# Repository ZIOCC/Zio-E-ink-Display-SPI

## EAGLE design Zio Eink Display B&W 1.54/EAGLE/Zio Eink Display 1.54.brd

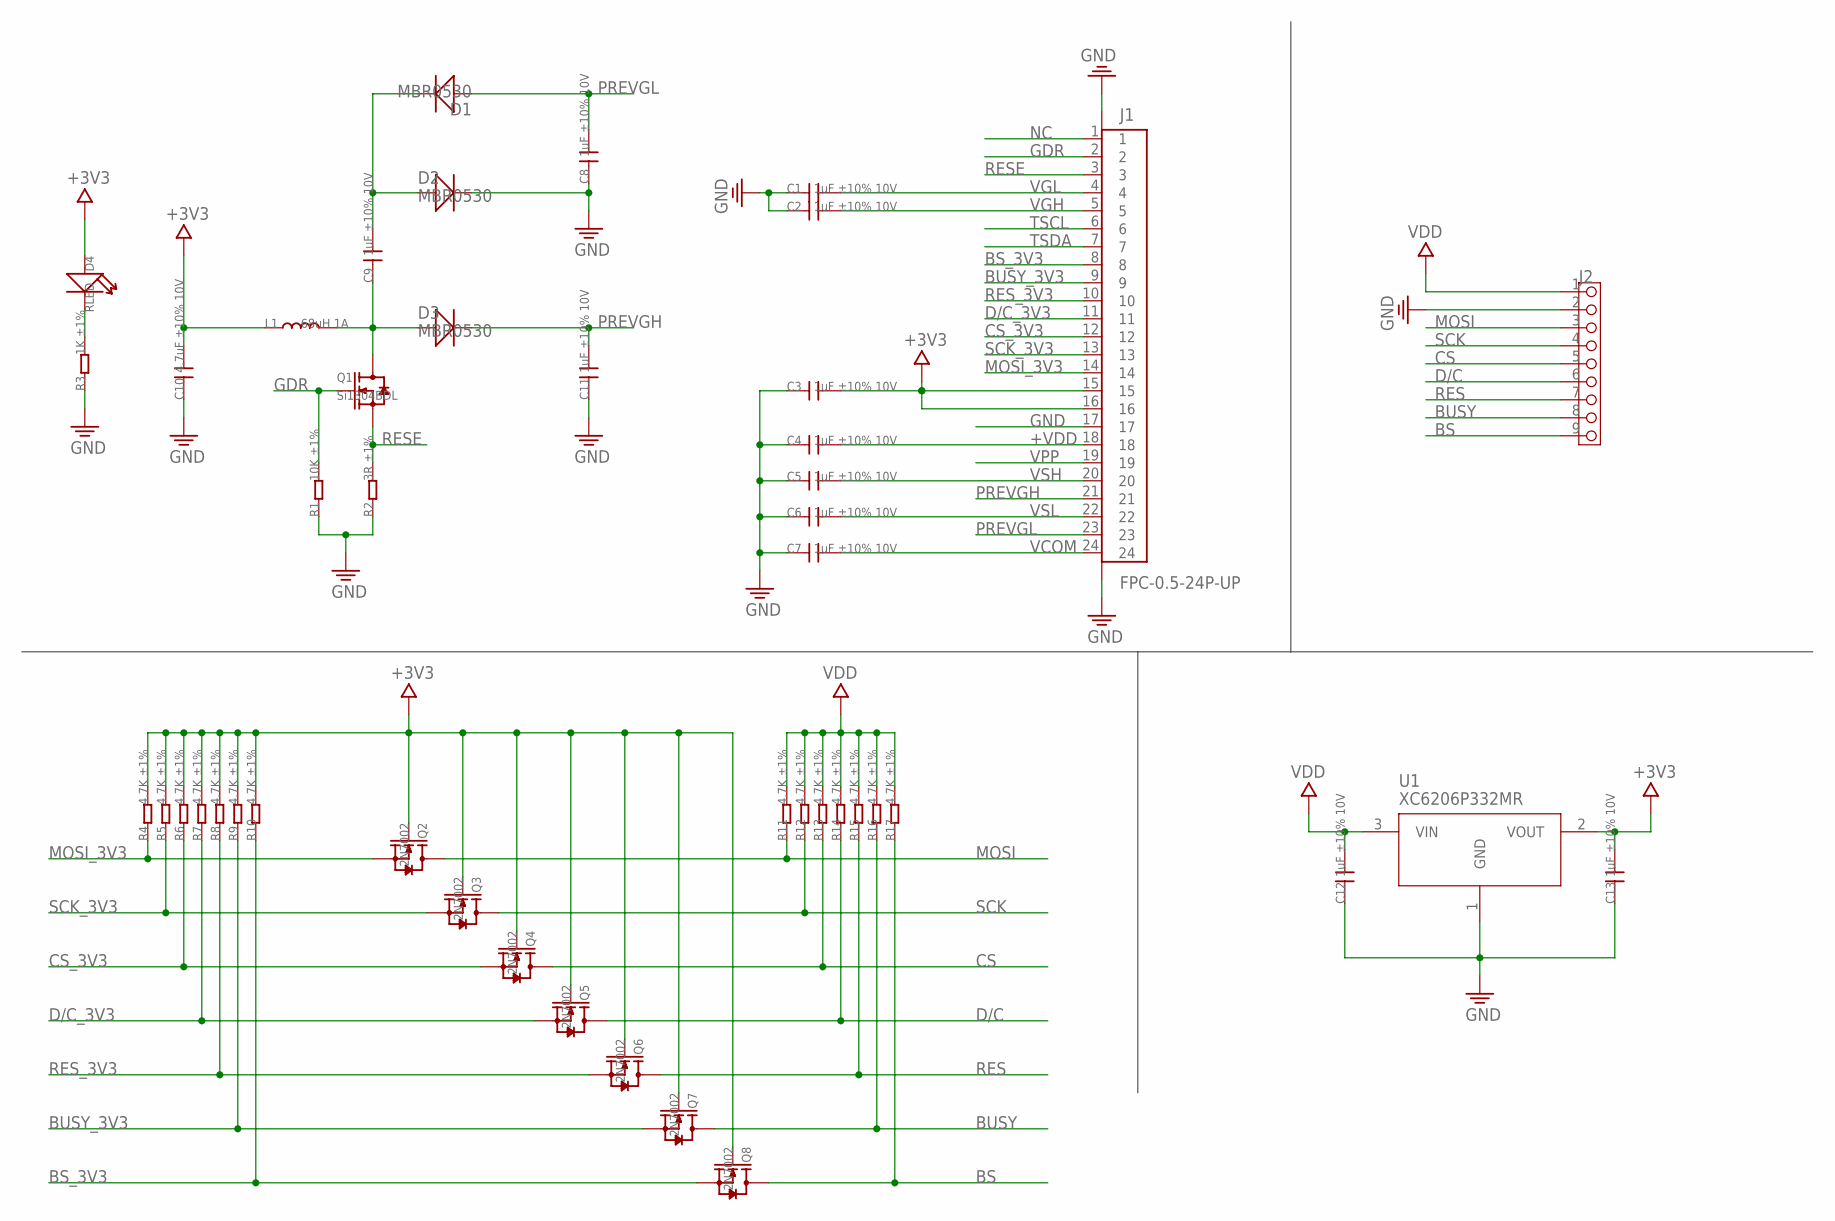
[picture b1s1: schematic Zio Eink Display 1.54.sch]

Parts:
C1, C2, C3, C4, C5, C6, C7, C8, C9, C11, C12, C13: 1uF ±10% 10V; 0603
C10: 4.7uF ±10% 10V; 0603
D1, D2, D3: MBR0530; SOD123
D4: RLED; LED-0603
J1: FPC-0.5-24P-UP; FPC-0.5-24P_UP
J2: HEADER-9P2.54; 9P-2.54-SMD
L1: 68uH 1A; L3012
Q1: Si1304BDL; SOT-323
Q2, Q3, Q4, Q5, Q6, Q7, Q8: 2N7002; SOT23
R1: 10K ±1%; 0603
R2: 3R ±1%; 0603
R3: 1K ±1%; 0402
R4, R5, R6, R7, R8, R9, R10, R11, R12, R13, R14, R15, R16, R17: 4.7K ±1%; 0402
U1: XC6206P332MR; SOT23

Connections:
+3V3: C3.2, C10.2, C13.2, D4.+, J1.15, J1.16, L1.P$1 (1), Q2.1 (G), Q3.1 (G), Q4.1 (G), Q5.1 (G), Q6.1 (G), Q7.1 (G), Q8.1 (G), R4.2, R5.2, R6.2, R7.2, R8.2, R9.2, R10.2, U1.2 (VOUT)
+VDD: C4.2, J1.18
BS: J2.9, Q8.3 (D), R17.1
BS_3V3: J1.8, Q8.2 (S), R10.1
BUSY: J2.8, Q7.3 (D), R16.1
BUSY_3V3: J1.9, Q7.2 (S), R9.1
CS: J2.5, Q4.3 (D), R13.1
CS_3V3: J1.12, Q4.2 (S), R6.1
D/C: J2.6, Q5.3 (D), R14.1
D/C_3V3: J1.11, Q5.2 (S), R7.1
GDR: J1.2, Q1.1 (G), R1.2
GND: C1.1, C2.1, C3.1, C4.1, C5.1, C6.1, C7.1, C8.1, C10.1, C11.1, C12.1, C13.1, D2.-, J1.17, J1.25 (G1), J1.26 (G2), J2.2, R1.1, R2.1, R3.1, U1.1 (GND)
MOSI: J2.3, Q2.3 (D), R11.1
MOSI_3V3: J1.14, Q2.2 (S), R4.1
unnamed: C9.2, D1.-, D2.+
unnamed: C9.1, D3.+, L1.P$2 (2), Q1.3 (D)
unnamed: D4.-, R3.2
NC: J1.1
PREVGH: C11.2, D3.-, J1.21
PREVGL: C8.2, D1.+, J1.23
RES: J2.7, Q6.3 (D), R15.1
RESE: J1.3, Q1.2 (S), R2.2
RES_3V3: J1.10, Q6.2 (S), R8.1
SCK: J2.4, Q3.3 (D), R12.1
SCK_3V3: J1.13, Q3.2 (S), R5.1
TSCL: J1.6
TSDA: J1.7
VCOM: C7.2, J1.24
VDD: C12.2, J2.1, R11.2, R12.2, R13.2, R14.2, R15.2, R16.2, R17.2, U1.3 (VIN)
VGH: C2.2, J1.5
VGL: C1.2, J1.4
VPP: J1.19
VSH: C5.2, J1.20
VSL: C6.2, J1.22

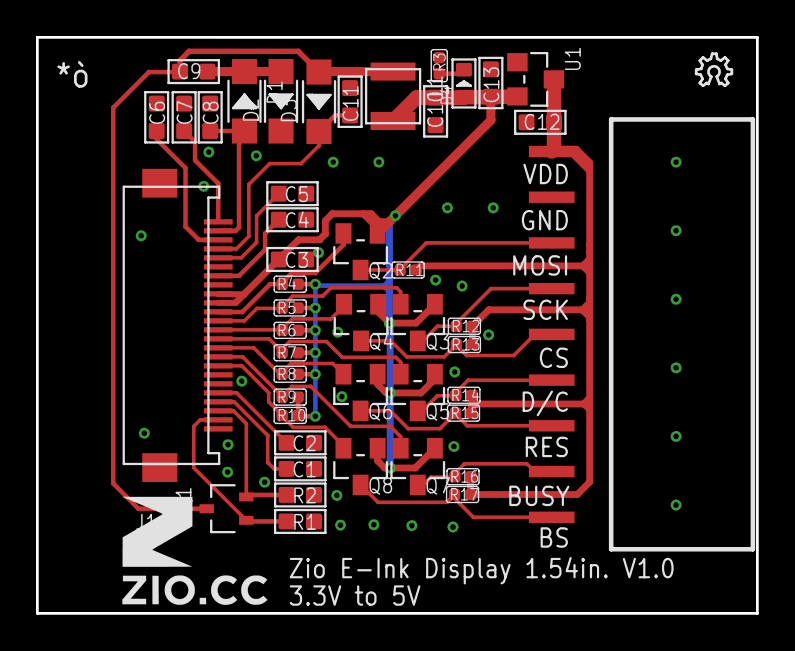
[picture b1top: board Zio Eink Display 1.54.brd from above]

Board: 2 copper layers, 40.0 x 32.0 mm, 48 parts (0 on the bottom side), 30 nets.

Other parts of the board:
U$9: 6MM
U$10: OSHW_6X70_NOTEXT
